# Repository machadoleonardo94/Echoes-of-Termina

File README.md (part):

# Echoes of Termina

An audio-visual devkit built from simple parts: a battery-powered ESP32 board with
a stereo speaker output, addressable LEDs, a microSD card and two buttons — plus the
desktop tool that authors the lightshows it plays.

| | |
|---|---|
| **Hardware** | ESP32-WROOM-32 board, 2x MAX98357A I2S amplifiers, WS2812B output, microSD, TP4056 charger, 2 buttons |
| **Firmware** | Bluetooth A2DP sink, local SD playback, `.echoes` lightshow decoder, Wi-Fi control panel |
| **Desktop** | Python/PySide6 editor: drop in an MP3, design the LED animation, upload the project to the board |
| **Status** | v0.8.0 pre-release — bench bring-up done, mask full board validation pending |

The project is three separable pieces that meet at the microSD card and the
`.echoes` script format: `Hardware/` (KiCad boards), `Firmware/` (PlatformIO /
Arduino for ESP32), and `Executable/` (the Windows editor and analyser).

---

## Hardware

Deliberately small bill of materials — an ESP32 module, two I2S class-D amplifiers, a
microSD socket, a charging IC, a handful of passives and the LED chain.

| Block | Part | Notes |
|---|---|---|
| MCU | ESP32-WROOM-32 N8R2 / 32UE | 8 MB flash, 2 MB PSRAM (see the pinout caveat below) |
| Speaker output | 2x MAX98357A (I2S) | stereo pair, channel chosen per amplifier by solder jumper; 4 Ω / 3 W drivers on PicoBlade connectors |
| Microphone input | INMP441 on I2S_NUM_1 | wired and pinned out, **not tested and not coded** |
| Storage | microSD over 1-bit SDMMC | CLK / CMD / D0; hinged socket on the mask boards, spring-loaded tray on Echoes V2 |
| LED output | 5 V WS2812B data line (`Strip_out`) | 1 to 200 pixels, brightness ceiling scaled to the count |
| Charging | TP4056 + USB-C | charge status LEDs |
| Power | AP2112K-3.3, PMOS latch on `latch_enable` | 2x 220 uF polymer + 100 nF decoupling |
| Buttons | PROG (GPIO0, active low) + external (active high) | polled, debounced gesture layer |

### Boards

| Directory | What it is |
|---|---|
| `Hardware/PCBs/Echoes_of_Termina/` | The bench devkit board — the reference for the pinout and the first board to come up |
| `Hardware/PCBs/Echoes_V2/` | A second board revision kept as the upgrade path from `Echoes_of_Termina` — the bench board that takes a spring-loaded microSD tray |
| `Hardware/PCBs/Marajoara_V3/` | The mask board: ESP32-WROOM-32UE, 10 onboard WS2812B, DF13 ports for the LED strips, PSRAM usable |
| `Hardware/PCBs/Marajoara_V2/`, `Hardware/PCBs/Marajoara_PCB/` | Earlier revisions, kept for reference and upgrade paths |
| `Hardware/PCBs/LED breakout boards/Top_6_WS2812B/`, `Mid_2_WS2812B/`, `Bottom_8_WS2812B/` | Small daisy-chained LED carrier strips for the mask (6 / 2 / 8 pixels) |
| `Hardware/Printed parts/Basic Echoes case/` | Enclosure STLs for the bench board, plus its Fusion 360 archive (`Echoes box.f3z`) |
| `Hardware/Printed parts/Speaker_40mm_Case/` | Parametric OpenSCAD case for a 40 mm driver, with measured acoustics — see its own [README](Hardware/Printed%20parts/Speaker_40mm_Case/README.md) |

Every KiCad project lives under `Hardware/PCBs/` in its own directory, with that
board's fabrication outputs in its `production/` subdirectory; enclosure and printed
parts live under `Hardware/Printed parts/`.

The ESP32-C3 variant in `Media/` and `Firmware/Marajoara-C3/` has no board directory
here: it is legacy, has no microSD slot and no audio stage, and keeps its show in
internal flash instead.

### Pinout

Compile-time, selected per environment (`src/shared/pinout.h`); defining two
boards, or none, is a build error rather than a silent fallback.

| Signal | Echoes V1 (bench) | Marajoara V3 |
|---|---|---|
| I2S speaker DOUT / BCLK / LRC | 16 / 17 / 18 | 13 / 27 / 18 |
| I2S mic SCK / WS / SD | 27 / 26 / 34 | 26 / 25 / 34 |
| microSD CLK / CMD / D0 | 14 / 15 / 2 | 14 / 15 / 2 |
| LED data | 25 | 23 |
| Second LED data *(planned)* | — | 33 |
| Charger `CHRG#` / `STDBY#` *(planned)* | — | 4 / 35 |
| External button | 4 | 19 |
| Power latch | 13 | 32 |
| ADC input | 36 | 36 |
| I2C SDA / SCL | 21 / 22 | 21 / 22 |

The two rows marked *planned* belong to the next Marajoara revision, which is awaiting
manual routing and DRC; no built board carries them yet. They are recorded here because
that revision closes the pin budget: GPIO39 is then the only free pin, with GPIO5 and
GPIO12 left to their strapping roles and GPIO1/GPIO3 to the UART0 console. On V3 the
external button input is fed by a touch module, which presents itself as an ordinary
active-high press — no firmware difference.

The module's PSRAM chip owns GPIO16 and GPIO17 internally. Echoes V1 puts I2S on
both of those pins, so that environment must build with PSRAM disabled — the pinout
header asserts this and refuses to compile a contradictory combination. Marajoara V3
moved the amplifier onto pins the 1-bit SD bus no longer needs, which is what makes
PSRAM usable there.

---

## Firmware

Two mutually exclusive modes, chosen at boot from NVS and switchable at runtime:

**Bluetooth mode** — the board is an A2DP sink (`ESP32-A2DP`). The phone streams SBC
over the air, the sink decodes it and drives I2S directly: no file, no card. Feedback
tones and the volume overlay are mixed into the same output path.

**Wi-Fi mode** — the board joins a network (WiFiManager captive portal) and serves an
HTTP control panel on port 80, advertising itself over mDNS as `echoes.local`. The
portal lists the card, starts and pauses playback, sets volume, adjusts the LED strip,
manages files, stages a firmware image and reboots.

Local playback is the ESP32-audioI2S decoder reading MP3/AAC/WAV from the card —
there is no OPUS or Vorbis decoder in the firmware, which is why the editor
transcodes.

### Lightshow playback

`.echoes` scripts are not loaded into RAM. The decoder streams them off the card with
the playhead, so exactly one command is resident at a time and a long show costs the
same memory as a short one; seeks and rewinds re-scan from the start of the file. A
file that is not time-sorted is rejected at load rather than played as a burst.

A show follows the SD player's position. The same engine also runs a standalone show
with the radio switched off, which is what makes a card-plus-battery mask work
without a phone or a network.

### Two-button interface

Two buttons, one gesture engine. `services/buttons.h` turns pin levels into
debounced gestures and knows nothing else; `services/controls.h` decides what each
gesture does — it is the only place the interface is defined, so the map below can be
argued about (and changed) without touching the state machine.

| Button | Pin | Idle level | Note |
|---|---|---|---|
| `PROG` | GPIO0 | high, press shorts to GND | onboard boot button, single-purpose |
| `EXT` | GPIO4 | low, press feeds 3V3 | external button; a touch module on Marajoara V3 presents the same active-high press |

#### Gesture map

| Gesture | When it fires | `PROG` (GPIO0) | `EXT` (GPIO4) |
|---|---|---|---|
| **click** | released before 600 ms — and, on `EXT`, no further press within 400 ms | play / pause — with nothing loaded in Wi-Fi mode, starts a standalone show | next song — with nothing loaded in Wi-Fi mode, starts a standalone show |
| **double** | two presses in one burst | — | cycle the LED animation: none → envelope → FFT |
| **triple** | three presses in one burst | — | switch mode (reboots the board) |
| **hold / repeat** | still down at 600 ms, then one repeat every 150 ms | volume down, 5 % per tick | volume up, 5 % per tick |
| **very long** | still down at 4000 ms | restart the current song | bring Wi-Fi back after a standalone show tore it down |

The two buttons are deliberately asymmetric. `PROG` is single-purpose, so its clicks
are committed **the instant the button comes up** — no 400 ms wait. `EXT` carries the
full multi-click ladder, and only its clicks pay that window, because at the moment of
release a second tap may still be coming. The window is a per-button property
(`multi_gap_ms`), not a global constant.

#### How a press is classified

Every press must survive a 25 ms debounce before the ladder even sees it. Then,
per button:

| Tier | Fires when | Result |
|---|---|---|
| `MIN_PRESS` | the press ends within 50 ms of starting | discarded as an electrical blip; an open click burst is left untouched |
| `CLICK` | released before 600 ms | `BTN_EV_CLICK` — `PROG` commits it on release; `EXT` waits 400 ms with no further press first |
| `DOUBLE` | two presses in one burst (`EXT` only) | `BTN_EV_DOUBLE` |
| `TRIPLE` | three presses in one burst (`EXT` only) | `BTN_EV_TRIPLE` — a fourth press stays a triple |
| `HOLD` | still down at 600 ms | `BTN_EV_HOLD`, then `BTN_EV_REPEAT` every 150 ms, then `BTN_EV_RELEASE` on let-go |
| `VERY_LONG` | still down at 4000 ms | `BTN_EV_VERY_LONG` once — it stops the repeat train |

A hold swallows the burst it interrupted: press-press-hold is a `HOLD`, never a
`DOUBLE` followed by a hold. A very-long hold also undoes the volume ramp its own
first four seconds performed, so "restart this song" never leaves the volume yanked to
one end.

#### Feedback

Each action answers back, because the two backends look identical from the outside:

- **Tones** — `audio_cues.h` mixes short cues into the audio (play, pause, next,
  confirm, deny, mode-switch arpeggio, and a rising/falling volume tick whose pitch
  reports the level; cues mix after volume control so they stay audible at any
  setting).
- **Strip overlay** — `ui_feedback.h` draws a volume bar while a ramp runs; the
  animation cycle blinks 1 / 2 / 3 times in blue to say *which* animation was landed
  on (the audio-reactive modes otherwise look identical while silent); a triple-click
  gets three blocking white flashes before the reboot; the very-long Wi-Fi restore
  gets two green flashes.
- **Serial log** — every gesture prints `[BTN] PROG/EXT <event> (<held> ms)`.

The diagnostic build (`echoes-v1-btn`, `-DBUTTON_TRACE=1`) logs every raw edge and a
5-second idle-level census for both pins, so a dead wire or stuck button is visible
immediately — and it refuses the destructive gestures (mode switch, standalone show)
so a misread cannot cost the verification session.

The full evaluation, including measured press timings, the state diagrams and the
design decisions behind the map, is in
[`Firmware/echoes_of_termina/docs/two-button-ui.md`](Firmware/echoes_of_termina/docs/two-button-ui.md).

### Portal API

| Route | Purpose |
|---|---|
| `GET /api/status`, `/api/files` | device state, directory listing |
| `POST /api/play`, `/api/stop`, `/api/pause`, `/api/next`, `/api/prev` | transport |
| `POST /api/volume`, `/api/leds` | volume (persisted to NVS), strip length and brightness |
| `POST /api/upload`, `/api/download`, `/api/delete`, `/api/rmdir`, `/api/mkdir`, `/api/rename` | file management |
| `POST /api/stage-firmware`, `/api/reboot` | SD firmware update |

### Update paths

- **OTA (over the air, from the computer):** ArduinoOTA on boards in Wi-Fi mode (`espota`
  upload). The image travels over the network and is applied live.
- **Drop-in update (recommended, from the SD card):** an app image on the card as
  `/firmware.bin`, applied when the board is power-cycled — before Wi-Fi, I2S and the decoder
  claim RAM. How the image reached the card does not matter and the firmware cannot tell:
  `POST /api/stage-firmware` from a browser and a card moved to a PC reader both leave the same
  file in the same place.
- **Serial (first flash, from a USB-to-serial adapter on `PORT1`):** the bootloader and
  partition table — and the base image on a blank board — come from a PlatformIO session
  over the UART0 console on GPIO1/GPIO3. There is no data path over the USB-C connector,
  and no bridge to the card, by design; see the storage limitation below.
- **USB-C:** charging only. The connector carries power and nothing else, so once the
  board has a runnable image there is no reason to reach for a cable.

### Build

```powershell
cd Firmware\echoes_of_termina
pio run -e marajoara-v3            # mask board
pio run -e echoes-v1               # bench board
pio run -e echoes-v1 -t upload     # flash the bench board over OTA
```

| Environment | Board | Notes |
|---|---|---|
| `echoes-v1` | Echoes V1 | PSRAM disabled, 8 MB partitions |
| `esp32-N16` | Echoes V1 | 16 MB flash, no PSRAM |
| `marajoara-v3` | Marajoara V3 | PSRAM enabled |
| `echoes-v1-btn` | diagnostic | logs every button edge, refuses destructive gestures |
| `marajoara-v3-bench` | diagnostic | one-shot microSD throughput benchmark |

The two diagnostic environments are not release images.

---

## The script format

One command per line, absolute timestamps against the audio file, LED addresses given
as `*` (all), a range `7-8`, or a list `4,11`:

```
0:07.226  SET  150 150 0        4,11   # set a colour now
0:07.327  FADE 150 150 0 80     4,11   # decay it, 80 % brightness lost per second
0:13.599  RAMP 0:03 0 0 255 255 0 0 *  # blue to yellow over three seconds
```

`SET` writes a colour, `FADE` decays it at a rate, `RAMP` interpolates between a
start and an end colour across a duration. Fades are time-based rather than
frame-based, so a strip of any length animates at the same speed.

A project file keeps one `[TrackName]` section per track, and a track may carry a
human label after its header — shown in the editor's track selector, and ignored by
the firmware (which skips `[...]` lines entirely):

```
[Slot 4] Column + Eyes (Drums)
# Imported from notes.mid
# Mask sector: Column + Eyes
# Instrument: Drums

0:04.032  FADE 32 96 224 99  9-12
```

---

## Desktop editor

`Executable/echoes/` is a PySide6 application. You give it an MP3, it plays the track
while you place animations on the LED map, and it uploads the finished project to the
board over the portal — no cable, no card swap.

- LED canvas: the mask layout is loaded from DXF artwork in `assets/`, so redrawing
  the artwork moves the zones instead of requiring code changes. The default board is
  the 28-zone Majora mask; a plain strip is just a different layout.
- Script editor and command toolbox: add `SET`/`FADE`/`RAMP` at the current playhead
  with a click, with a timestamp readout driving the write position.
- Note highway and envelope views for timing against the music.
- Importers: Clone Hero `.chart` and MIDI, both mapped onto the LED ring so a chart
  becomes a lightshow without hand-authoring.
- Spectrum analyser window (also standalone via `Run Spectrum.bat`) for picking
  frequencies before deciding where an animation lives.
- Track slots, mixdown of multiple audio stems to one MP3, macro hotkeys, metadata
  (`song.ini`), and a hardware-version converter that remaps LED numbering between
  board revisions.
- Device panel: mDNS discovery of `echoes.local`, file browser, upload, and remote
  play/pause.

Requirements: Python 3.10+ with PySide6 (installed automatically on first run) and
`ffmpeg` on `PATH` if the source audio is not already MP3. Launch with
`Run Echoes.bat`.

An importer is included for translating .chart and .midi files used in Clone Hero projects.
The importer composes the label as `zone (instrument)` — "Column + Eyes" + MIDI track
`PART DRUMS` → `Column + Eyes (Drums)` (the `PART ` prefix is dropped and shouting
names are title-cased; a bare `.chart` section such as `ExpertSingle` contributes no
instrument) — and writes `# Mask sector:` / `# Instrument:` comments into the body so
the saved project documents where the track came from. The track selector shows the
label alone (falling back to the stored section name for unlabelled tracks), and
Script Properties labels its rows *Track 1..N* and lets you edit each label, whose
field shows the full `zone (instrument)` text. Merged mask exports carry no headers,
so labels never reach the board.

---

## Demo

| Clip | Shows |
|---|---|
| [Song of Storms test](Media/song-of-storms-test.mp4) | A `.echoes` lightshow played back on the mask |
| [FFT strip test](Media/fft-strip-test.mp4) | The generated spectrum animation driving a strip |

Additional board photos in `Media/`: `c3-testfit.jpg` and `c3-no-audio.jpg`
show the C3 variant. It is **legacy** — kept for the record and visible in the photos,
not a board to build today — and it differs from the ESP32 designs in ways that matter:
it has **no microSD slot** and no audio stage, so the show lives in the module's
internal flash filesystem (`LittleFS`, uploaded with `pio run -t uploadfs`), which is
about 1.4 MB on the 4 MB module against a card that is measured in gigabytes. That
build also reads the whole script into RAM rather than streaming it, supports `SET` and
`FADE` only, and drives a fixed 28-pixel chain. See `Firmware/Marajoara-C3/`.

| C3 test fit | C3 board, no audio stage |
|---|---|
|  |  |

---

## Repository layout

| Path | Contents |
|---|---|
| `Hardware/` | KiCad projects under `PCBs/` (each with its fabrication outputs), printed-part sources under `Printed parts/`, DXF artwork and STEP/STL models |
| `Firmware/echoes_of_termina/` | The ESP32 firmware — components, services, shared pinout, partition tables |
| `Firmware/Marajoara-C3/` | Legacy C3 build: lightshow player with no audio and no SD slot, shows held in the on-flash filesystem |
| `Executable/echoes/` | Desktop editor, FFT analyser, `projects/` folder, release builder |
| `Datasheets/` | Vendor datasheets (MAX98357A) |
| `Media/` | Photos, renders and demo clips used by this document |
| `dist/` | Packaged pre-releases: editor ZIP, firmware images, checksums |

---

## Status and known limitations

- **Bluetooth and SD playback both work**, but the portal cannot decode MP3 in
  parallel with serving the page. On a board without PSRAM the radio alone costs
  about 45 KB of internal RAM, and the I2S DMA buffers need ~32 KB of DMA-capable
  internal RAM before the decoder has any; below a free-heap threshold the portal
  drops Wi-Fi and hands the track to the standalone player instead. Design the
  feature around that rather than against it. The levers that should move it are in the
  build, not in the chip: `CONFIG_SPIRAM_ALLOW_BSS_SEG_EXTERNAL_MEMORY` puts the BSS of
  lwIP, net80211, pp and bt into PSRAM, `CONFIG_SPIRAM_TRY_ALLOCATE_WIFI_LWIP` prefers PSRAM
  for the Wi-Fi and lwIP buffers, and `CONFIG_SPIRAM_SPEED_80M` raises the card clock.
  **None of the three has been tried or measured** — they are the next experiment, on
  Marajoara V3, the only board here with PSRAM switched on. PSRAM does not delete the
  internal reserve even then: IDF holds back 32 KB of DMA-capable internal RAM regardless
  (`CONFIG_SPIRAM_MALLOC_RESERVE_INTERNAL`, default 32768), because DMA into external RAM
  has real limits.
- **The microphone is unbuilt.** The INMP441 is on the board and on its own I2S
  peripheral with its own pins, but there is no capture path in the firmware and
  nothing has been measured.
- **The C3 variant is legacy.** No microSD slot and no audio: a show has to fit in the
  module's internal flash, it is loaded into RAM wholesale rather than streamed, and
  the script dialect stops at `SET` and `FADE`. It survives in the photos and in
  `Firmware/Marajoara-C3/`, not as a supported target.
- If driving a large LED strip, the board cannot handle the FFT animation and audio gets choppy.
- The MAX98357A channel-select resistors decide which amplifier carries which channel;
  verify them per board before trusting a stereo test. The default value is 1M for (L+R)/2. Swap for 10k for Left channel, and 220k for Right Channel
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
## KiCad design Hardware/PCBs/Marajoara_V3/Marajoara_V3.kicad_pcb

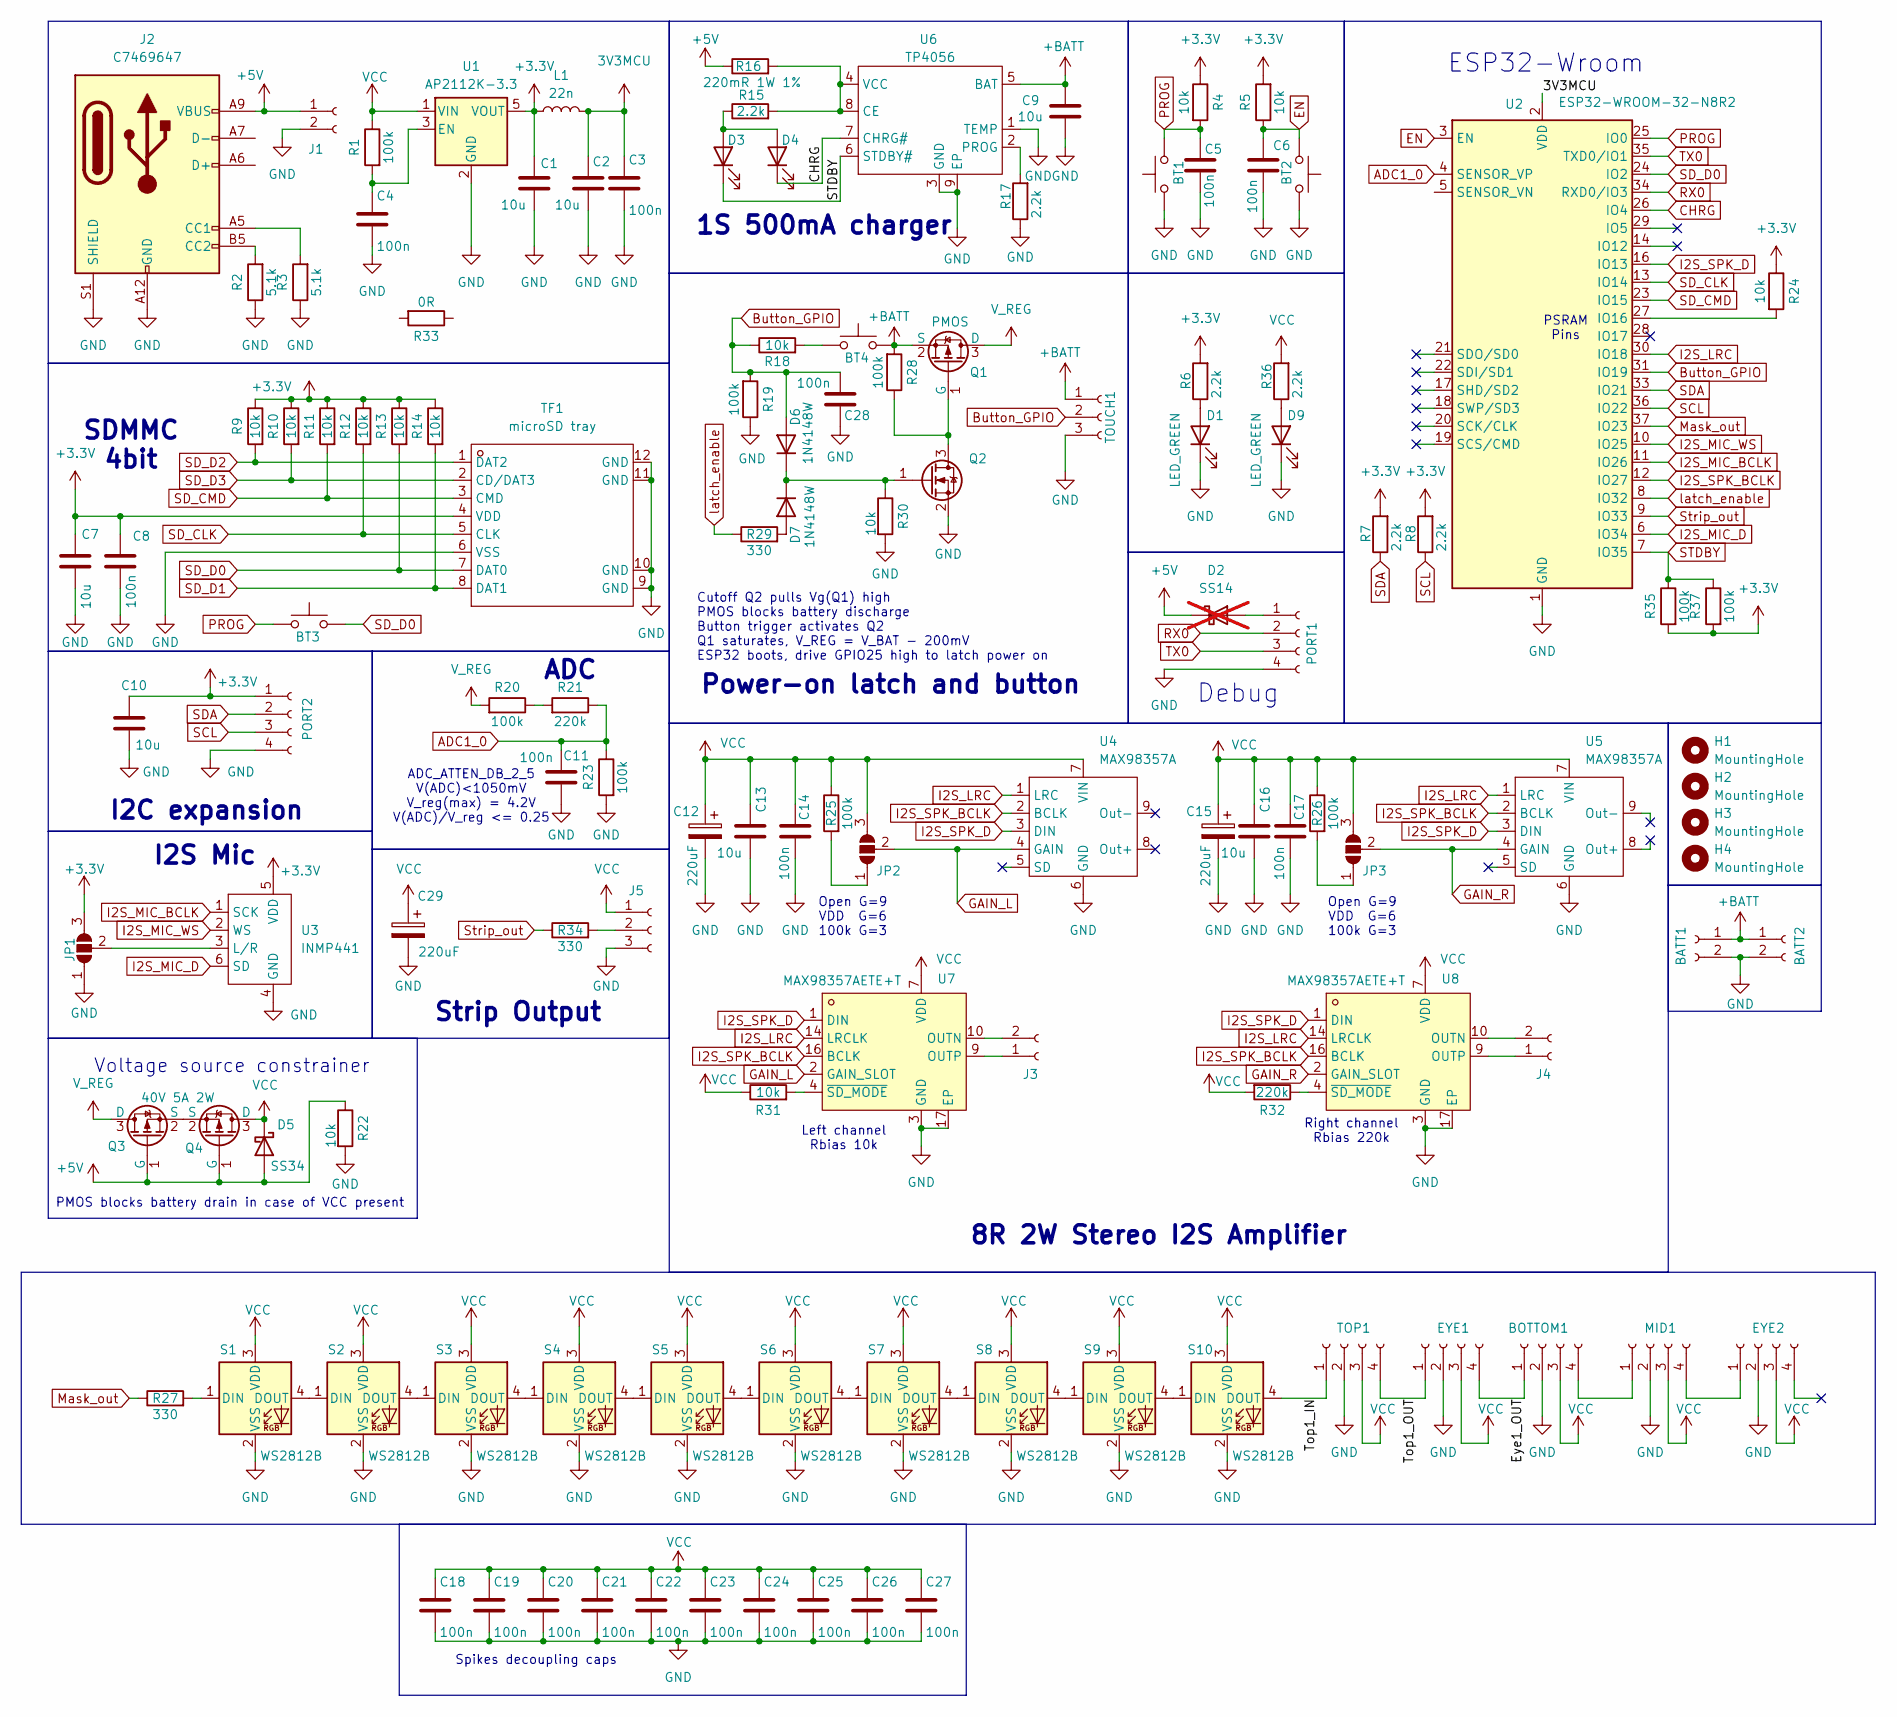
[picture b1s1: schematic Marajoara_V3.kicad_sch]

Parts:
BATT1, BATT2: Conn_01x02_Socket; Molex_KK-254_AE-6410-02A_1x02_P2.54mm_Vertical; LCSC C49023803
BOTTOM1: Conn_01x04_Socket; Hirose_DF13C_CL535-0404-8-51_1x04-1MP_P1.25mm_Vertical; LCSC C7433470
BT1, BT2, BT3, BT4: SW_Push; SW_SPST_PTS647_Sx38; LCSC C2888502
C1, C2, C7, C9, C10, C13, C16: 10u; C_0805_2012Metric_Pad1.18x1.45mm_HandSolder; LCSC C162422
C3, C4, C5, C6, C8, C11, C14, C17, C18, C19, C20, C21, C22, C23, C24, C25, C26, C27, C28: 100n; C_0805_2012Metric_Pad1.18x1.45mm_HandSolder; LCSC C49678
C12, C15: 220uF; Cap_polymer; LCSC C2162971
C29: 220uF; Cap_polymer; Mfr. Part Number 35TKV220M8X10.5; LCSC C2162971
D1, D9: LED_GREEN; LED_0805_2012Metric_Pad1.15x1.40mm_HandSolder; LCSC C84256
D2: SS14; D_SMA; LCSC C2480; not fitted
D3: LED_BLUE; LED_0805_2012Metric_Pad1.15x1.40mm_HandSolder; LCSC C965817
D4: LED_RED; LED_0805_2012Metric_Pad1.15x1.40mm_HandSolder; LCSC C84256
D5: SS34; D_SMC_Handsoldering; Mfr. Part Number SS34; LCSC C8678
D6, D7: 1N4148W; D_SOD-123; LCSC C83528
EYE1, EYE2: Conn_01x04_Socket; Hirose_DF13C_CL535-0404-8-51_1x04-1MP_P1.25mm_Vertical; LCSC C7433470
H1, H2, H3, H4: MountingHole; MountingHole_3.2mm_M3
J1: Conn_01x02_Socket; Molex_KK-254_AE-6410-02A_1x02_P2.54mm_Vertical; LCSC C49023803
J2: USB_C_Receptacle_USB2.0_8P; USB-C-SMD_GT-USB-7101A; LCSC C7469647
J3, J4: Conn_01x02_Socket; Molex_PicoBlade_53261-0271_1x02-1MP_P1.25mm_Horizontal; LCSC C7433468
J5: Conn_01x03_Socket; TerminalBlock_Xinya_XY308-2.54-3P_1x03_P2.54mm_Horizontal
JP1, JP2, JP3: SolderJumper_3_Open; SolderJumper-3_P1.3mm_Open_RoundedPad1.0x1.5mm
L1: 22n; L_0805_2012Metric_Pad1.05x1.20mm_HandSolder; LCSC C108962
MID1: Conn_01x04_Socket; Hirose_DF13C_CL535-0404-8-51_1x04-1MP_P1.25mm_Vertical; LCSC C7433470
PORT1, PORT2: Conn_01x04_Socket; Hirose_DF13C_CL535-0404-8-51_1x04-1MP_P1.25mm_Vertical; LCSC C7433470
Q1, Q3, Q4: PMOS; SOT-23_Handsoldering; LCSC C42456992
Q2: 2N7002K; SOT-23; LCSC C65189
R1, R19, R20, R23, R25, R26, R28, R35, R37: 100k; R_0805_2012Metric_Pad1.20x1.40mm_HandSolder; LCSC C149504
R2, R3: 5.1k; R_0805_2012Metric_Pad1.20x1.40mm_HandSolder; LCSC C27834
R4, R5, R9, R10, R11, R12, R13, R14, R18, R22, R24, R30, R31: 10k; R_0805_2012Metric_Pad1.20x1.40mm_HandSolder; LCSC C17414
R6, R7, R8, R15, R17, R36: 2.2k; R_0805_2012Metric_Pad1.20x1.40mm_HandSolder; LCSC C17520
R16: 220mR 1W 1%; R_1206_3216Metric_Pad1.30x1.75mm_HandSolder; LCSC C2683384
R21, R32: 220k; R_0805_2012Metric_Pad1.20x1.40mm_HandSolder; LCSC C149504
R27, R29, R34: 330; R_0805_2012Metric_Pad1.20x1.40mm_HandSolder; LCSC C17630
R33: 0R; R_0805_2012Metric_Pad1.20x1.40mm_HandSolder; LCSC 1
S1, S2, S3, S4, S5, S6, S7, S8, S9, S10: WS2812B; WS2812B_PTH_staggered
TF1: microSD tray; TF-SMD_TF-CARD-XG8P-H1.5; LCSC Part Name 翻盖式 MicroSD卡(TF卡) 卡座
TOP1: Conn_01x04_Socket; Hirose_DF13C_CL535-0404-8-51_1x04-1MP_P1.25mm_Vertical; LCSC C7433470
TOUCH1: Conn_01x03_Socket; PinHeader_1x03_P2.54mm_Vertical
U1: AP2112K-3.3; SOT-23-5; LCSC C51118
U2: ESP32-WROOM-32-N8R2; ESP32-WROOM-32UE; LCSC C5361945
U3: INMP441; INMP441 Module
U4, U5: MAX98357A; LCSC C910544
U6: TP4056; ESOP-8_L4.9-W3.9-P1.27-LS6.0-BL-EP; LCSC Part Name 1A锂电池充电IC
U7, U8: MAX98357AETE+T; TQFN-16_L3.0-W3.0-P0.50-BL-EP1.5; MPN MAX98357AETE+T; LCSC Part C910544

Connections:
3V3MCU: C2.1, C3.1, L1.2, U2.2 (VDD)
+3.3V: C1.1, C7.1, C8.2, C10.1, JP1.3 (B), L1.1, PORT2.1, R4.1, R5.2, R6.2, R7.2, R8.2, R9.1, R10.1, R11.1, R12.1, R13.1, R14.1, R24.1, R35.2, R37.2, TF1.4 (VDD), U1.5 (VOUT), U3.5 (VDD)
+5V: D2.1 (K), D5.2 (A), J1.1, J2.A9 (VBUS), J2.B9 (VBUS), Q3.1 (G), Q4.1 (G), R16.1, R22.1
+BATT: BATT1.1, BATT2.1, BT4.1, C9.1, Q1.2 (S), R28.2, TOUCH1.1, U6.5 (BAT)
/Eye1_OUT: BOTTOM1.1, EYE1.4
/Top1_IN: S10.4 (DOUT), TOP1.1
/Top1_OUT: EYE1.1, TOP1.4
ADC1_0: C11.2, R21.1, R23.1, U2.4 (SENSOR_VP)
Button_GPIO: C28.2, D6.2 (A), R18.1, R19.2, TOUCH1.2, U2.31 (IO19)
EN: BT2.2, C6.1, R5.1, U2.3 (EN)
GAIN_L: JP2.2 (C), U4.4 (GAIN), U7.2 (GAIN_SLOT)
GAIN_R: JP3.2 (C), U5.4 (GAIN), U8.2 (GAIN_SLOT)
GND: BATT1.2, BATT2.2, BOTTOM1.2, BT1.1, BT2.1, C1.2, C2.2, C3.2, C4.2, C5.2, C6.2, C7.2, C8.1, C9.2, C10.2, C11.1, C12.2, C13.2, C14.1, C15.2, C16.2, C17.1, C18.2, C19.2, C20.2, C21.2, C22.2, C23.2, C24.2, C25.2, C26.2, C27.2, C28.1, C29.2, D1.1 (K), D9.1 (K), EYE1.2, EYE2.2, J1.2, J2.A12 (GND), J2.B12 (GND), J2.S1 (SHIELD), J5.3, JP1.1 (A), MID1.2, PORT1.4, PORT2.4, Q2.2 (S), R2.1, R3.1, R17.1, R19.1, R22.2, R23.2, R30.2, S1.2 (VSS), S2.2 (VSS), S3.2 (VSS), S4.2 (VSS), S5.2 (VSS), S6.2 (VSS), S7.2 (VSS), S8.2 (VSS), S9.2 (VSS), S10.2 (VSS), TF1.6 (VSS), TF1.9 (GND), TF1.10 (GND), TF1.11 (GND), TF1.12 (GND), TOP1.2, TOUCH1.3, U1.2 (GND), U2.1 (GND), U2.15 (GND), U2.38 (GND), U2.39 (GND), U3.4 (GND), U4.6 (GND), U5.6 (GND), U6.1 (TEMP), U6.3 (GND), U6.9 (EP), U7.3 (GND), U7.11 (GND), U7.15 (GND), U7.17 (EP), U8.3 (GND), U8.11 (GND), U8.15 (GND), U8.17 (EP)
I2S_LRC: U2.30 (IO18), U4.1 (LRC), U5.1 (LRC), U7.14 (LRCLK), U8.14 (LRCLK)
I2S_MIC_BCLK: U2.11 (IO26), U3.1 (SCK)
I2S_MIC_D: U2.6 (IO34), U3.6 (SD)
I2S_MIC_WS: U2.10 (IO25), U3.2 (WS)
I2S_SPK_BCLK: U2.12 (IO27), U4.2 (BCLK), U5.2 (BCLK), U7.16 (BCLK), U8.16 (BCLK)
I2S_SPK_D: U2.16 (IO13), U4.3 (DIN), U5.3 (DIN), U7.1 (DIN), U8.1 (DIN)
Mask_out: R27.1, U2.37 (IO23)
unnamed: BOTTOM1.4, MID1.1
unnamed: BT4.2, R18.2
unnamed: D1.2 (A), R6.1
unnamed: D3.2 (A), D4.2 (A), R15.1
unnamed: D3.1 (K), U6.6 (STDBY#)
unnamed: D4.1 (K), U6.7 (CHRG#)
unnamed: D6.1 (K), D7.1 (K), Q2.1 (G), R30.1
unnamed: D7.2 (A), R29.2
unnamed: D9.2 (A), R36.1
unnamed: EYE2.1, MID1.4
unnamed: J2.A5 (CC1), R3.2
unnamed: J2.B5 (CC2), R2.2
unnamed: J3.1, U7.9 (OUTP)
unnamed: J3.2, U7.10 (OUTN)
unnamed: J4.1, U8.9 (OUTP)
unnamed: J4.2, U8.10 (OUTN)
unnamed: J5.2, R34.2
unnamed: JP1.2 (C), U3.3 (L/R)
unnamed: JP2.1 (A), R25.2
unnamed: JP3.1 (A), R26.2
unnamed: D2.2 (A), PORT1.1
unnamed: Q1.1 (G), Q2.3 (D), R28.1
unnamed: Q3.2 (S), Q4.2 (S)
unnamed: R20.1, R21.2
unnamed: R35.1, R37.1, U2.7 (IO35)
unnamed: R27.2, S1.1 (DIN)
unnamed: S1.4 (DOUT), S2.1 (DIN)
unnamed: S2.4 (DOUT), S3.1 (DIN)
unnamed: S3.4 (DOUT), S4.1 (DIN)
unnamed: S4.4 (DOUT), S5.1 (DIN)
unnamed: S5.4 (DOUT), S6.1 (DIN)
unnamed: S6.4 (DOUT), S7.1 (DIN)
unnamed: S7.4 (DOUT), S8.1 (DIN)
unnamed: S8.4 (DOUT), S9.1 (DIN)
unnamed: S9.4 (DOUT), S10.1 (DIN)
unnamed: C4.1, R1.2, U1.3 (EN)
unnamed: R24.2, U2.27 (IO16)
unnamed: R15.2, R16.2, U6.4 (VCC), U6.8 (CE)
unnamed: R17.2, U6.2 (PROG)
unnamed: R31.2, U7.4 (~SD_MODE)
unnamed: R32.1, U8.4 (~SD_MODE)
PROG: BT1.2, BT3.2, C5.1, R4.2, U2.25 (IO0)
RX0: PORT1.2, U2.34 (RXD0/IO3)
SCL: PORT2.3, R8.1, U2.36 (IO22)
SDA: PORT2.2, R7.1, U2.33 (IO21)
SD_CLK: R12.2, TF1.5 (CLK), U2.13 (IO14)
SD_CMD: R11.2, TF1.3 (CMD), U2.23 (IO15)
SD_D0: BT3.1, R13.2, TF1.7 (DAT0), U2.24 (IO2)
SD_D2: R9.2, TF1.1 (DAT2)
SD_D3: R10.2, TF1.2 (CD/DAT3)
Strip_out: R34.1, U2.9 (IO33)
TX0: PORT1.3, U2.35 (TXD0/IO1)
latch_enable: R29.1, U2.8 (IO32)

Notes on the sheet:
PMOS blocks battery drain in case of VCC present
Right channel Rbias 220k
I2S Mic
Open G=9 VDD G=6 100k G=3
Power-on latch and button
8R 2W Stereo I2S Amplifier
ADC_ATTEN_DB_2_5 V(ADC)<1050mV V_reg(max) = 4.2V V(ADC)/V_reg <= 0.25
ADC
Spikes decoupling caps
SDMMC 4bit
Left channel Rbias 10k
I2C expansion
Cutoff Q2 pulls Vg(Q1) high PMOS blocks battery discharge Button trigger activates Q2 Q1 saturates, V_REG = V_BAT - 200mV ESP32 boots, drive GPIO25 high to latch power on
Strip Output
PSRAM Pins
Debug
Voltage source constrainer
ESP32-Wroom
1S 500mA charger

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
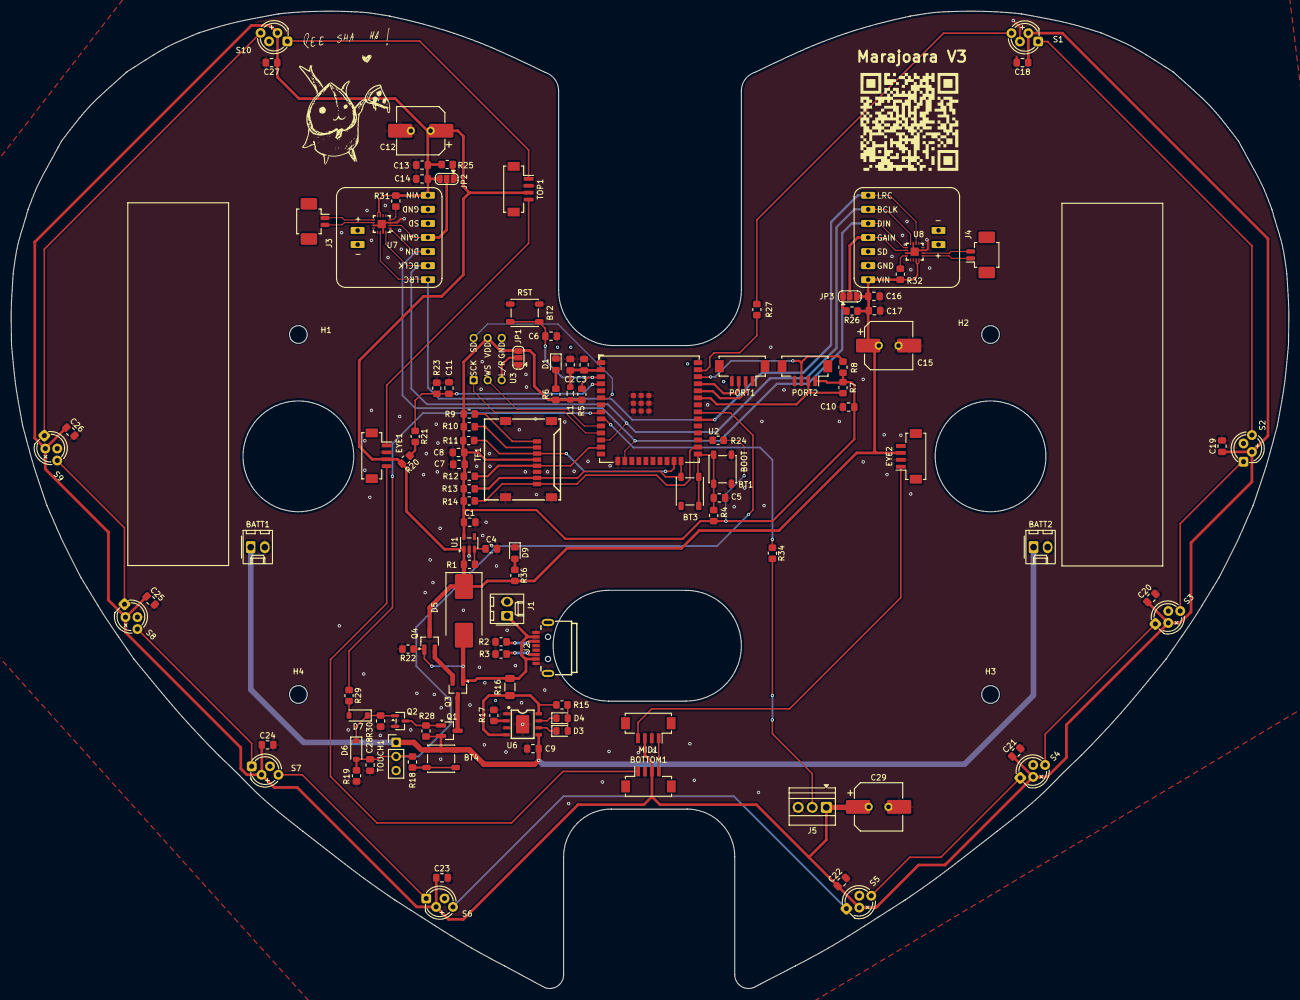
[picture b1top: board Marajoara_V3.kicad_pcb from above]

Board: 2 copper layers, 230.7 x 176.5 mm, 121 parts (1 on the bottom side), 74 nets.

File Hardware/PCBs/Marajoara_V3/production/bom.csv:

Designator,Footprint,Quantity,Value,LCSC Part #
"BATT1, BATT2, J1",Molex_KK-254_AE-6410-02A_1x02_P2.54mm_Vertical,3,Conn_01x02_Socket,C49023803
"BOTTOM1, EYE1, EYE2, MID1, PORT1, PORT2, TOP1",Hirose_DF13C_CL535-0404-8-51_1x04-1MP_P1.25mm_Vertical,7,Conn_01x04_Socket,C7433470
"BT1, BT2, BT3, BT4",SW_SPST_PTS647_Sx38,4,SW_Push,C2888502
"C1, C10, C13, C16, C2, C7, C9",0805,7,10u,C162422
"C11, C14, C17, C18, C19, C20, C21, C22, C23, C24, C25, C26, C27, C28, C3, C4, C5, C6, C8",0805,19,100n,C49678
"C12, C15, C29",Cap_polymer,3,220uF,C2162971
"D1, D9",0805,2,LED_GREEN,C84256
D3,0805,1,LED_BLUE,C965817
D4,0805,1,LED_RED,C84256
D5,D_SMC_Handsoldering,1,SS34,C8678
"D6, D7",D_SOD-123,2,1N4148W,C83528
J2,USB-C-SMD_GT-USB-7101A,1,USB_C_Receptacle_USB2.0_8P,C7469647
"J3, J4",Molex_PicoBlade_53261-0271_1x02-1MP_P1.25mm_Horizontal,2,Conn_01x02_Socket,C7433468
J5,TerminalBlock_Xinya_XY308-2.54-3P_1x03_P2.54mm_Horizontal,1,Conn_01x03_Socket,
L1,0805,1,22n,C108962
"Q1, Q3, Q4",SOT-23_Handsoldering,3,PMOS,C42456992
Q2,SOT-23,1,2N7002K,C65189
"R1, R19, R20, R23, R25, R26, R28",0805,7,100k,C149504
"R10, R11, R12, R13, R14, R18, R22, R24, R30, R31, R4, R5, R9",0805,13,10k,C17414
"R15, R17, R36, R6, R7, R8",0805,6,2.2k,C17520
R16,1206,1,220mR 1W 1%,C2683384
"R2, R3",0805,2,5.1k,C27834
"R21, R32",0805,2,220k,C149504
"R27, R29, R34",0805,3,330,C17630
R33,0805,1,0R,1
"S1, S10, S2, S3, S4, S5, S6, S7, S8, S9",WS2812B_PTH_staggered,10,WS2812B,
TF1,TF-SMD_TF-CARD-XG8P-H1.5,1,microSD tray,
TOUCH1,PinHeader_1x03_P2.54mm_Vertical,1,Conn_01x03_Socket,
U1,SOT-23-5,1,AP2112K-3.3,C51118
U2,ESP32-WROOM-32UE,1,ESP32-WROOM-32-N8R2,C5361945
U3,INMP441 Module,1,INMP441,
U6,ESOP-8_L4.9-W3.9-P1.27-LS6.0-BL-EP,1,TP4056,C382139
"U7, U8",TQFN-16_L3.0-W3.0-P0.50-BL-EP1.5,2,MAX98357AETE+T,C910544

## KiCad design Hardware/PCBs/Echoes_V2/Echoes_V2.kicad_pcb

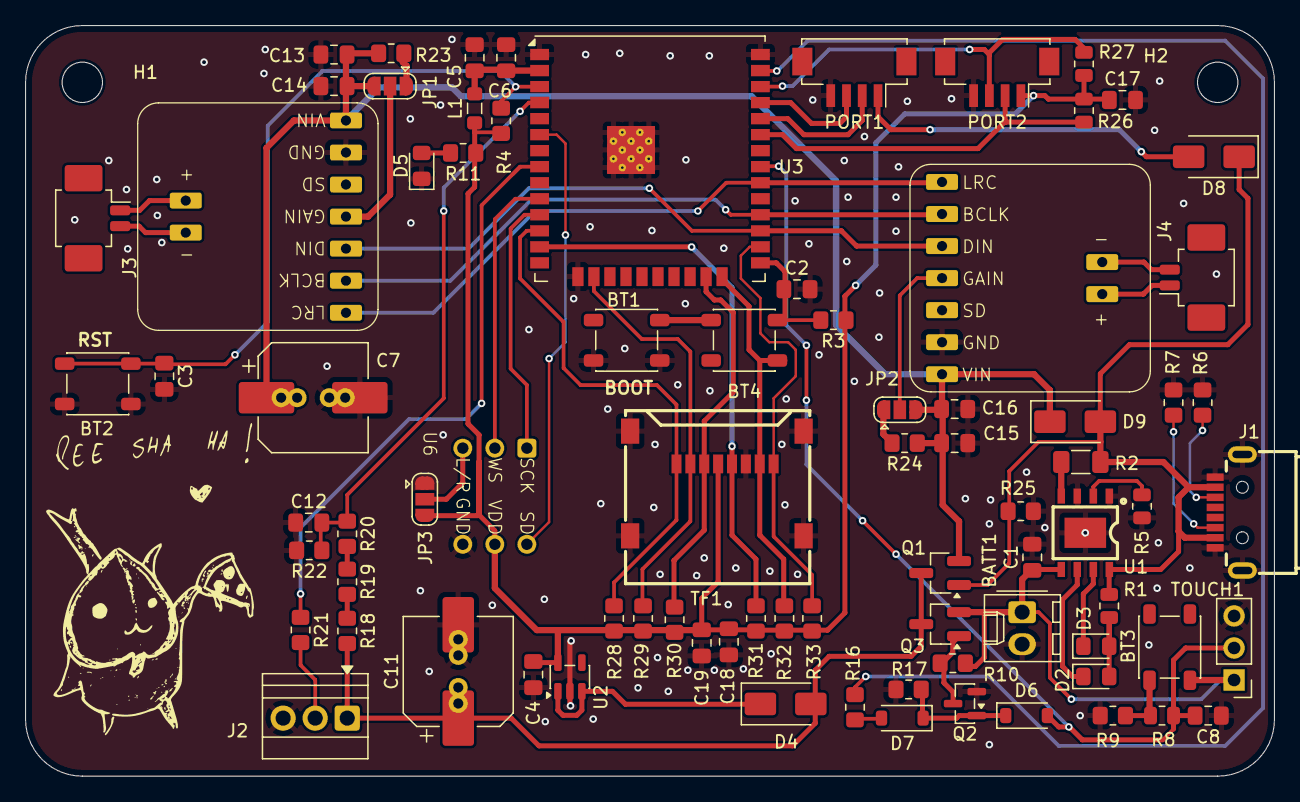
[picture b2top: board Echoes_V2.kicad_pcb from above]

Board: 2 copper layers, 99.0 x 59.5 mm, 82 parts (0 on the bottom side), 55 nets.

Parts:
BATT1: Conn_01x02_Socket; Molex_KK-254_AE-6410-02A_1x02_P2.54mm_Vertical
BT1, BT2, BT3, BT4: SW_Push; SW_SPST_PTS647_Sx38
C1, C4, C5, C13, C15, C17, C18: 10u; C_0805_2012Metric_Pad1.18x1.45mm_HandSolder
C2, C3, C6, C8, C12, C14, C16, C19: 100n; C_0805_2012Metric_Pad1.18x1.45mm_HandSolder
C7, C11: 220uF; Cap_polymer
D2: LED_BLUE; LED_0805_2012Metric_Pad1.15x1.40mm_HandSolder
D3: LED_RED; LED_0805_2012Metric_Pad1.15x1.40mm_HandSolder
D4, D8, D9: SS14; D_SMA
D5: LED_GREEN; LED_0805_2012Metric_Pad1.15x1.40mm_HandSolder
D6, D7: 1N4148W; D_SOD-123
H1, H2: MountingHole; MountingHole_3.2mm_M3
J1: USB_C_Receptacle_USB2.0_8P; USB-C-SMD_GT-USB-7101A
J2: Conn_01x03_Socket; TerminalBlock_Xinya_XY308-2.54-3P_1x03_P2.54mm_Horizontal
J3, J4: Conn_01x02_Socket; Molex_PicoBlade_53261-0271_1x02-1MP_P1.25mm_Horizontal
JP1, JP2, JP3: SolderJumper_3_Open; SolderJumper-3_P1.3mm_Open_RoundedPad1.0x1.5mm
L1: 22n; L_0805_2012Metric_Pad1.05x1.20mm_HandSolder
PORT1, PORT2: Conn_01x04_Socket; Hirose_DF13C_CL535-0404-8-51_1x04-1MP_P1.25mm_Vertical
Q1, Q3: PMOS; SOT-23_Handsoldering
Q2: 2N7002K; SOT-23
R1, R5, R8, R26, R27: 2.2k; R_0805_2012Metric
R2: 220mR 1W 1%; R_1206_3216Metric_Pad1.30x1.75mm_HandSolder
R3, R4, R17, R28, R29, R30, R31, R32, R33: 10k; R_0805_2012Metric_Pad1.20x1.40mm_HandSolder
R6, R7: 5.1k; R_0805_2012Metric_Pad1.20x1.40mm_HandSolder
R9, R10, R18, R19, R20, R22, R23, R24, R25: 100k; R_0805_2012Metric_Pad1.20x1.40mm_HandSolder
R11, R16, R21: 330; R_0805_2012Metric_Pad1.20x1.40mm_HandSolder
TF1: microSD tray; TF-SMD_TF-CARD-XG8P-H1.5
TOUCH1: Conn_01x03_Socket; PinHeader_1x03_P2.54mm_Vertical
U1: TP4056; ESOP-8_L4.9-W3.9-P1.27-LS6.0-BL-EP
U2: AP2112K-3.3; SOT-23-5
U3: ESP32-WROOM-32U-N8; ESP32-WROOM-32U
U4, U5: MAX98357A
U6: INMP441; INMP441 Module

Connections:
3V3MCU: C5.1, C6.1, L1.2, U3.2 (VDD)
+3.3V: C4.1, C17.1, C18.1, C19.2, JP3.3 (B), L1.1, PORT2.1, R3.1, R4.2, R11.1, R26.2, R27.2, R28.1, R29.1, R30.1, R31.1, R32.1, R33.1, TF1.4 (VDD), U2.5 (VOUT), U6.5 (VDD)
+5V: D8.1 (K), D9.2 (A), J1.A9 (VBUS), J1.B9 (VBUS), Q3.1 (G), R1.1, R2.1, R25.2, U1.8 (CE)
+BATT: BATT1.1, BT3.1, C1.1, Q1.2 (S), R10.2, TOUCH1.1, U1.5 (BAT)
ADC1_0: C12.2, R20.1, R22.1, U3.4 (SENSOR_VP)
Button_GPIO: C8.2, D6.2 (A), R8.2, TOUCH1.2, U3.31 (IO19)
EN: BT2.2, C3.1, R4.1, U3.3 (EN)
GND: BATT1.2, BT1.1, BT2.1, C1.2, C2.2, C3.2, C4.2, C5.2, C6.2, C7.2, C8.1, C11.2, C12.1, C13.2, C14.1, C15.2, C16.1, C17.2, C18.2, C19.1, D5.1 (K), J1.A12 (GND), J1.B12 (GND), J1.S1 (SHIELD), J2.3, JP3.1 (A), PORT1.4, PORT2.4, Q2.2 (S), R5.1, R6.1, R7.1, R9.1, R17.2, R22.2, R25.1, TF1.6 (VSS), TF1.9 (GND), TF1.10 (GND), TF1.11 (GND), TF1.12 (GND), TOUCH1.3, U1.1 (TEMP), U1.3 (GND), U1.9 (EP), U2.2 (GND), U3.1 (GND), U3.15 (GND), U3.38 (GND), U3.39 (GND), U4.6 (GND), U5.6 (GND), U6.4 (GND)
I2S_BCLK: U3.28 (IO17), U4.2 (BCLK), U5.2 (BCLK)
I2S_DOUT: U3.27 (IO16), U4.3 (DIN), U5.3 (DIN)
I2S_LRC: U3.30 (IO18), U4.1 (LRC), U5.1 (LRC)
MIC_SCK: U3.11 (IO26), U6.1 (SCK)
MIC_SD: U3.6 (IO34), U6.6 (SD)
MIC_WS: U3.10 (IO25), U6.2 (WS)
unnamed: BT3.2, R8.1, R9.2
unnamed: D2.2 (A), D3.2 (A), R1.2
unnamed: D2.1 (K), U1.6 (STDBY#)
unnamed: D3.1 (K), U1.7 (CHRG#)
unnamed: D4.1 (K), U2.1 (VIN), U2.3 (EN)
unnamed: D5.2 (A), R11.2
unnamed: D6.1 (K), D7.1 (K), Q2.1 (G), R17.1
unnamed: D7.2 (A), R16.2
unnamed: D8.2 (A), PORT1.1
unnamed: J1.A5 (CC1), R7.2
unnamed: J1.B5 (CC2), R6.2
unnamed: J2.2, R21.2
unnamed: J3.1, U4.8 (Out+)
unnamed: J3.2, U4.9 (Out-)
unnamed: J4.1, U5.8 (Out+)
unnamed: J4.2, U5.9 (Out-)
unnamed: JP1.1 (A), R23.2
unnamed: JP1.2 (C), U4.4 (GAIN)
unnamed: JP2.1 (A), R24.2
unnamed: JP2.2 (C), U5.4 (GAIN)
unnamed: JP3.2 (C), U6.3 (L/R)
unnamed: Q1.1 (G), Q2.3 (D), R10.1
unnamed: R18.1, R19.2
unnamed: R19.1, R20.2
unnamed: R5.2, U1.2 (PROG)
unnamed: R2.2, U1.4 (VCC)
PROG: BT1.2, BT4.2, C2.1, R3.2, U3.25 (IO0)
RX0: PORT1.2, U3.34 (RXD0/IO3)
SCL: PORT2.3, R27.1, U3.36 (IO22)
SDA: PORT2.2, R26.1, U3.33 (IO21)
SD_CLK: R31.2, TF1.5 (CLK), U3.13 (IO14)
SD_CMD: R30.2, TF1.3 (CMD), U3.23 (IO15)
SD_D0: BT4.1, R32.2, TF1.7 (DAT0), U3.24 (IO2)
SD_D1: R33.2, TF1.8 (DAT1), U3.26 (IO4)
SD_D2: R28.2, TF1.1 (DAT2), U3.12 (IO27)
SD_D3: R29.2, TF1.2 (CD/DAT3), U3.16 (IO13)
Strip_out: R21.1, U3.8 (IO32)
TX0: PORT1.3, U3.35 (TXD0/IO1)
V_REG: C11.1, D4.2 (A), J2.1, Q1.3 (D), Q3.3 (D), R18.2
V_SPK: C7.1, C13.1, C14.2, C15.1, C16.2, D9.1 (K), JP1.3 (B), JP2.3 (B), Q3.2 (S), R23.1, R24.1, U4.7 (VIN), U5.7 (VIN)
latch_enable: R16.1, U3.37 (IO23)

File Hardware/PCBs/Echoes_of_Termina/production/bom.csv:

Designator,Footprint,Quantity,Value,LCSC Part #
BATT1,Molex_KK-254_AE-6410-02A_1x02_P2.54mm_Vertical,1,Conn_01x02_Socket,C49023803
"BT1, BT2, BT3, BT4",SW_SPST_PTS647_Sx38,4,SW_Push,C2888502
"C1, C13, C15, C17, C18, C4, C5",0805,7,10u,C162422
"C11, C7",Cap_polymer,2,220uF,C2162971
"C12, C14, C16, C19, C2, C3, C6, C8",0805,8,100n,C49678
D2,0805,1,LED_BLUE,C965817
D3,0805,1,LED_RED,C84256
"D4, D8, D9",D_SMA,3,SS14,C2480
D5,0805,1,LED_GREEN,C84256
"D6, D7",D_SOD-123,2,1N4148W,C83528
J1,USB-C-SMD_GT-USB-7101A,1,USB_C_Receptacle_USB2.0_8P,C7469647
J2,TerminalBlock_Xinya_XY308-2.54-3P_1x03_P2.54mm_Horizontal,1,Conn_01x03_Socket,
"J3, J4",Molex_PicoBlade_53261-0271_1x02-1MP_P1.25mm_Horizontal,2,Conn_01x02_Socket,C7433468
L1,0805,1,22n,C108962
"PORT1, PORT2",Hirose_DF13C_CL535-0404-8-51_1x04-1MP_P1.25mm_Vertical,2,Conn_01x04_Socket,C7433470
"Q1, Q3",SOT-23_Handsoldering,2,PMOS,C42456992
Q2,SOT-23,1,2N7002K,C65189
"R1, R26, R27, R5, R8",0805,5,2.2k,C17520
"R10, R18, R19, R20, R22, R23, R24, R25, R9",0805,9,100k,C149504
"R11, R16, R21",0805,3,330,C17630
"R17, R28, R29, R3, R30, R31, R32, R33, R4",0805,9,10k,C17414
R2,1206,1,220mR 1W 1%,C2683384
"R6, R7",0805,2,5.1k,C27834
TF1,TF-SMD_TF-CARD-XG8P-H1.5,1,microSD tray,
TOUCH1,PinHeader_1x03_P2.54mm_Vertical,1,Conn_01x03_Socket,
U1,ESOP-8_L4.9-W3.9-P1.27-LS6.0-BL-EP,1,TP4056,C382139
U2,SOT-23-5,1,AP2112K-3.3,C51118
U3,ESP32-WROOM-32U,1,ESP32-WROOM-32U-N8,C5361945
"U4, U5",MAX98357A,2,MAX98357A,C910544
U6,INMP441 Module,1,INMP441,

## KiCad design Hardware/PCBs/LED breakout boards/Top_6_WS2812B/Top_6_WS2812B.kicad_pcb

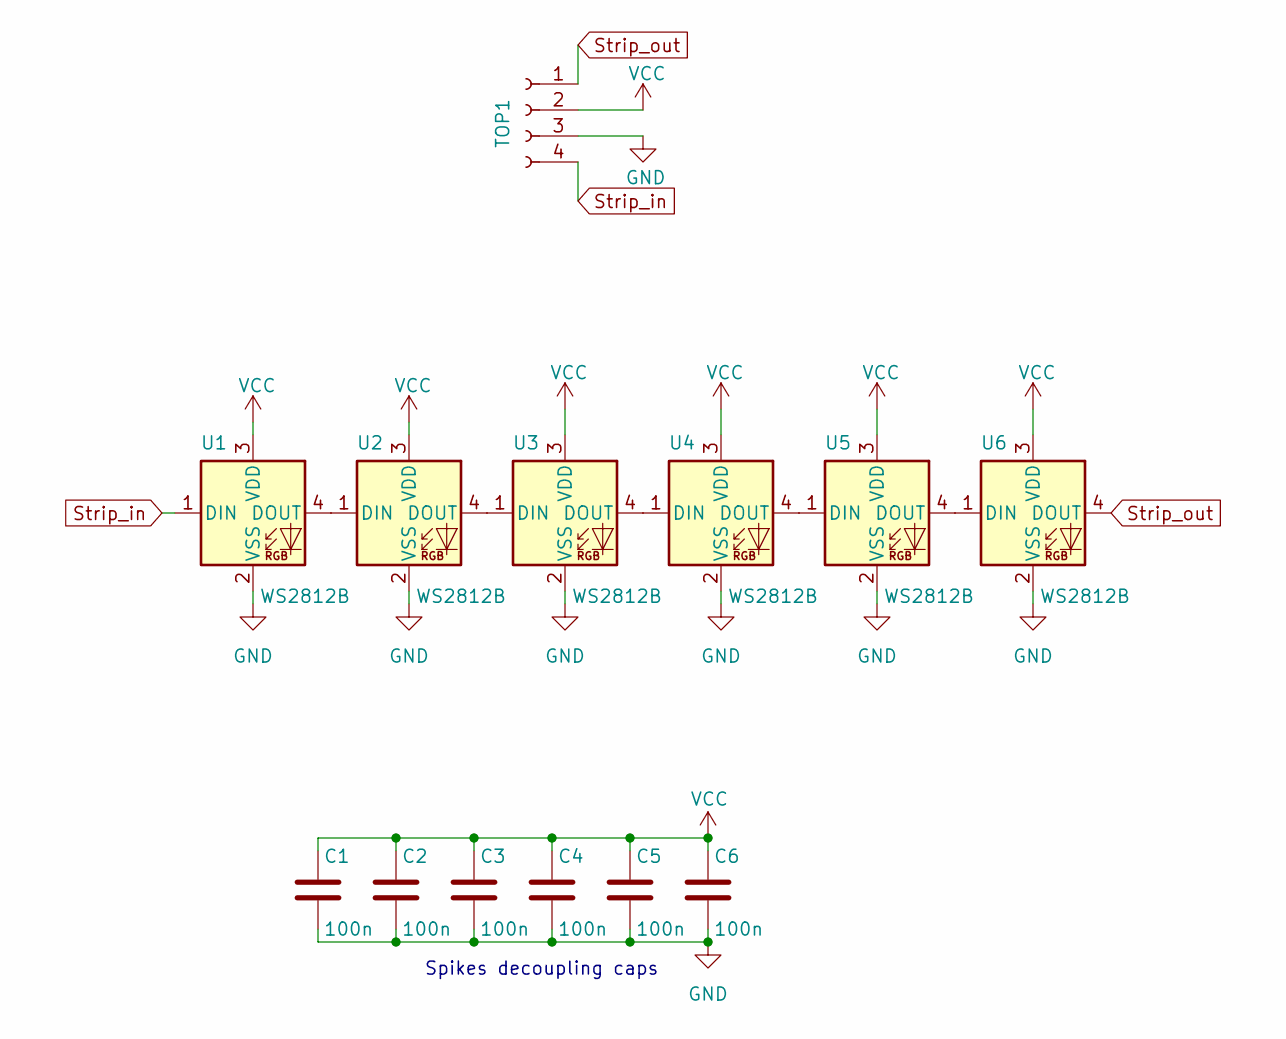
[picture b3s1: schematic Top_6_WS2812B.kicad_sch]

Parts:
C1, C2, C3, C4, C5, C6: 100n; C_0805_2012Metric_Pad1.18x1.45mm_HandSolder; LCSC C49678
TOP1: Conn_01x04_Socket; Hirose_DF13C_CL535-0404-8-51_1x04-1MP_P1.25mm_Vertical; LCSC C7433470
U1, U2, U3, U4, U5, U6: WS2812B; WS2812B_PTH_staggered

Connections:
GND: C1.2, C2.2, C3.2, C4.2, C5.2, C6.2, TOP1.3, U1.2 (VSS), U2.2 (VSS), U3.2 (VSS), U4.2 (VSS), U5.2 (VSS), U6.2 (VSS)
unnamed: U1.4 (DOUT), U2.1 (DIN)
unnamed: U2.4 (DOUT), U3.1 (DIN)
unnamed: U3.4 (DOUT), U4.1 (DIN)
unnamed: U4.4 (DOUT), U5.1 (DIN)
unnamed: U5.4 (DOUT), U6.1 (DIN)
Strip_in: TOP1.4, U1.1 (DIN)
Strip_out: TOP1.1, U6.4 (DOUT)
VCC: C1.1, C2.1, C3.1, C4.1, C5.1, C6.1, TOP1.2, U1.3 (VDD), U2.3 (VDD), U3.3 (VDD), U4.3 (VDD), U5.3 (VDD), U6.3 (VDD)

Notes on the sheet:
Spikes decoupling caps

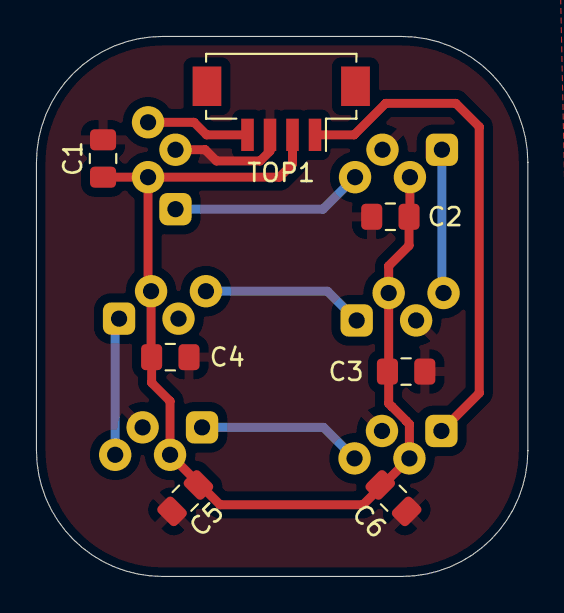
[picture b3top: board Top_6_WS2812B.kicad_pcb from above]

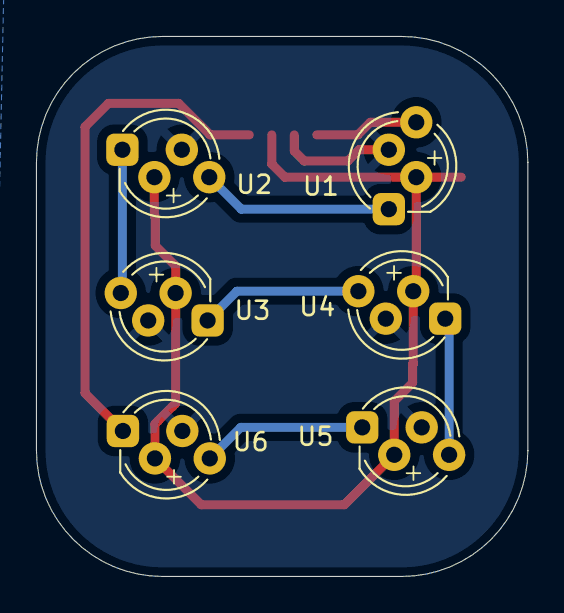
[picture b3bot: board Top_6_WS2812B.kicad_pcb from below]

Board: 2 copper layers, 27.3 x 30.0 mm, 13 parts (6 on the bottom side), 9 nets.

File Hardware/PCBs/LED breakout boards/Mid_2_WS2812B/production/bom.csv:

Designator,Footprint,Quantity,Value,LCSC Part #
"C1, C2",0805,2,100n,C49678
TOP1,Hirose_DF13C_CL535-0404-8-51_1x04-1MP_P1.25mm_Vertical,1,Conn_01x04_Socket,C7433470
"U1, U2",WS2812B_PTH_staggered,2,WS2812B,
